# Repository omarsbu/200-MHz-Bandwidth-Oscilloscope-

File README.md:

**This project is intended to be an improvement on a previous version that can be seen here:**
https://github.com/omarsbu/1MHz-Bandwidth-Oscilloscope/tree/main/100kHz%20Oscilloscope

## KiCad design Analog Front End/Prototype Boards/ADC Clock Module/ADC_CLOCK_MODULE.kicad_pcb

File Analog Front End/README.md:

The purpose of an analog front end is to condition the input signal so that it maximizes the ADC’s dynamic range and limits the bandwidth to the ADC’s Nyquist frequency. Attenuators extend the measurable range by scaling down large input signals to within the appropriate voltage range and a programmable gain amplifier boosts small signals so they make full use of the ADC’s resolution. DC offsetting is also applied to bias the signal so that it fits well within the ADC’s input range. A high impedance JFET LNA buffer allows the oscilloscope input to be terminated with 1 MΩ or 50 Ω impedance.

The input stage of each channel consists of a set of relay switches to select between AC and DC coupling, as well as different attenuation levels. A compensated 1 MΩ L-pad attenuator is used for normal measurements with standard probes, while 50 Ω pi-attenuators are used for high-fidelity measurements from a 50 Ω source. Protection diodes clamp the input voltage if it exceeds the positive or negative supply rails.

The BUF802 is used in conjunction with the OPA140 to form a composite amplifier that delivers strong performance at both high and low frequencies. The BUF802, with its JFET input, provides exceptional AC performance but poor DC precision, while the OPA140 offers excellent DC precision but lacks sufficient bandwidth and slew rate for high-frequency signals. To leverage the strengths of both, the main input is AC-coupled to the BUF802, while the auxiliary input is driven by the OPA140’s DC offset circuitry. This circuitry uses a differential amplifier along with a DAC (0–5 V) and a 2.5 V reference to shift the output within a programmable range of ±2.5 V. A resistor in series with the differential amplifier output allows the DAC to modify the DC feedback network to the OPA140, which drives the BUF802 auxiliary input, thereby enabling a programmable DC offset of the input signal. To prevent the BUF802 output from exceeding the ±1 V differential input range of the LMH6518, Zener diodes are used to clamp the output to ±1 V. Additionally, a 50 Ω series resistor allows the BUF802 to drive the subsequent stages of the analog front-end signal chain as a 50 Ω source.

The ideal input condition of the LMH6518 are shown below:

The LMH6552 functions as a level shifter and single-ended to differential converter with 0 dB gain, providing a balanced differential input with a 2.5 V common-mode voltage to the LMH6518. The single-ended input to the LMH6552 is clamped to ±1 V by the BUF802, ensuring that the LMH6552’s differential output is also limited to ±1 V. The LMH6518 includes programmable bandwidth-limiting filters for anti-aliasing, and its output common-mode voltage is set to match the ADC’s common-mode voltage.

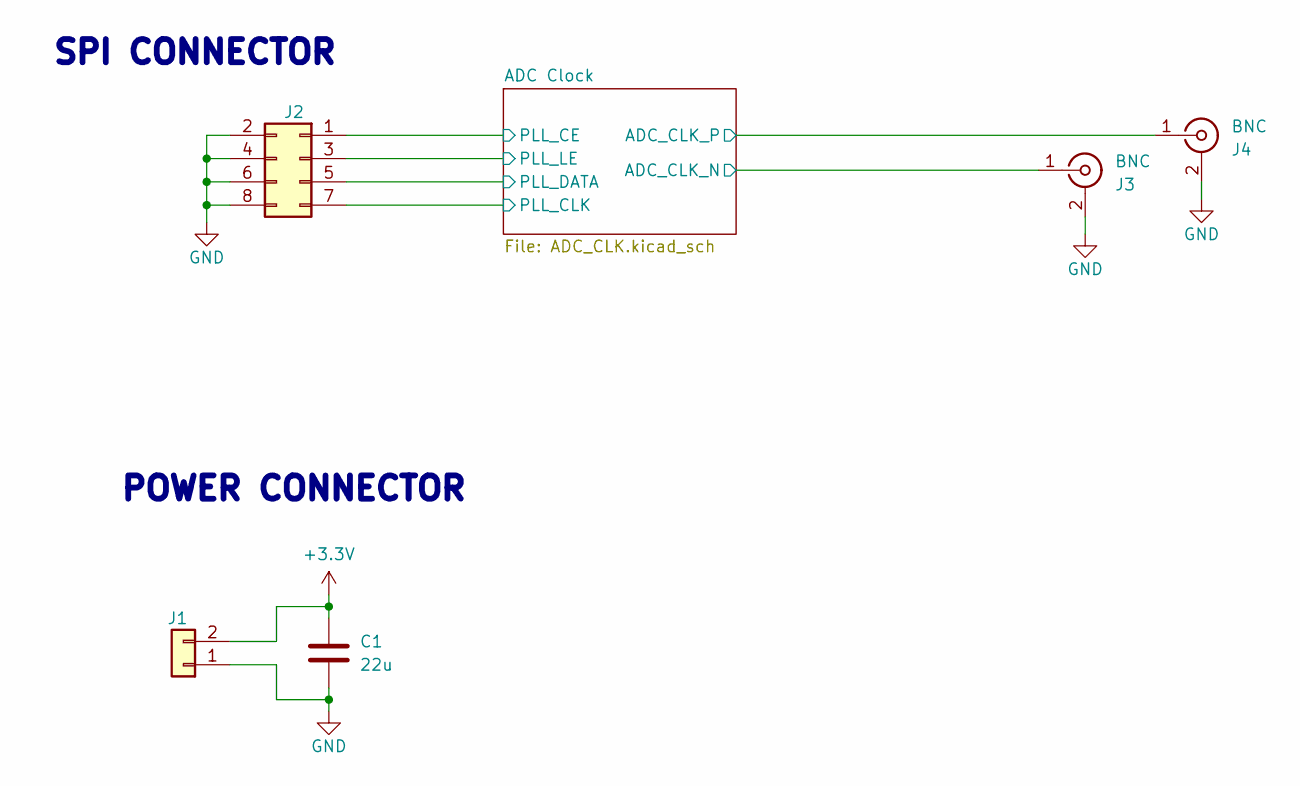
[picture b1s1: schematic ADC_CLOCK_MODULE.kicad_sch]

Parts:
C1: 22u; C_1210_3225Metric_Pad1.33x2.70mm_HandSolder
J1: Conn_01x02; PinHeader_1x02_P2.54mm_Vertical
J2: Conn_02x04_Odd_Even; PinHeader_2x04_P2.54mm_Vertical
J3, J4: BNC; SMA_Amphenol_132289_EdgeMount

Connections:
+3.3V: C1.1, J1.2; also elsewhere on the board
/ADC Clock/ADC_CLK_N: J3.1 (In); also elsewhere on the board
/ADC Clock/ADC_CLK_P: J4.1 (In); also elsewhere on the board
/ADC Clock/PLL_CE: J2.1; also elsewhere on the board
/ADC Clock/PLL_CLK: J2.7; also elsewhere on the board
/ADC Clock/PLL_DATA: J2.5; also elsewhere on the board
/ADC Clock/PLL_LE: J2.3; also elsewhere on the board
GND: C1.2, J1.1, J2.2, J2.4, J2.6, J2.8, J3.2 (Ext), J4.2 (Ext); also elsewhere on the board

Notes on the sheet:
SPI CONNECTOR
POWER CONNECTOR

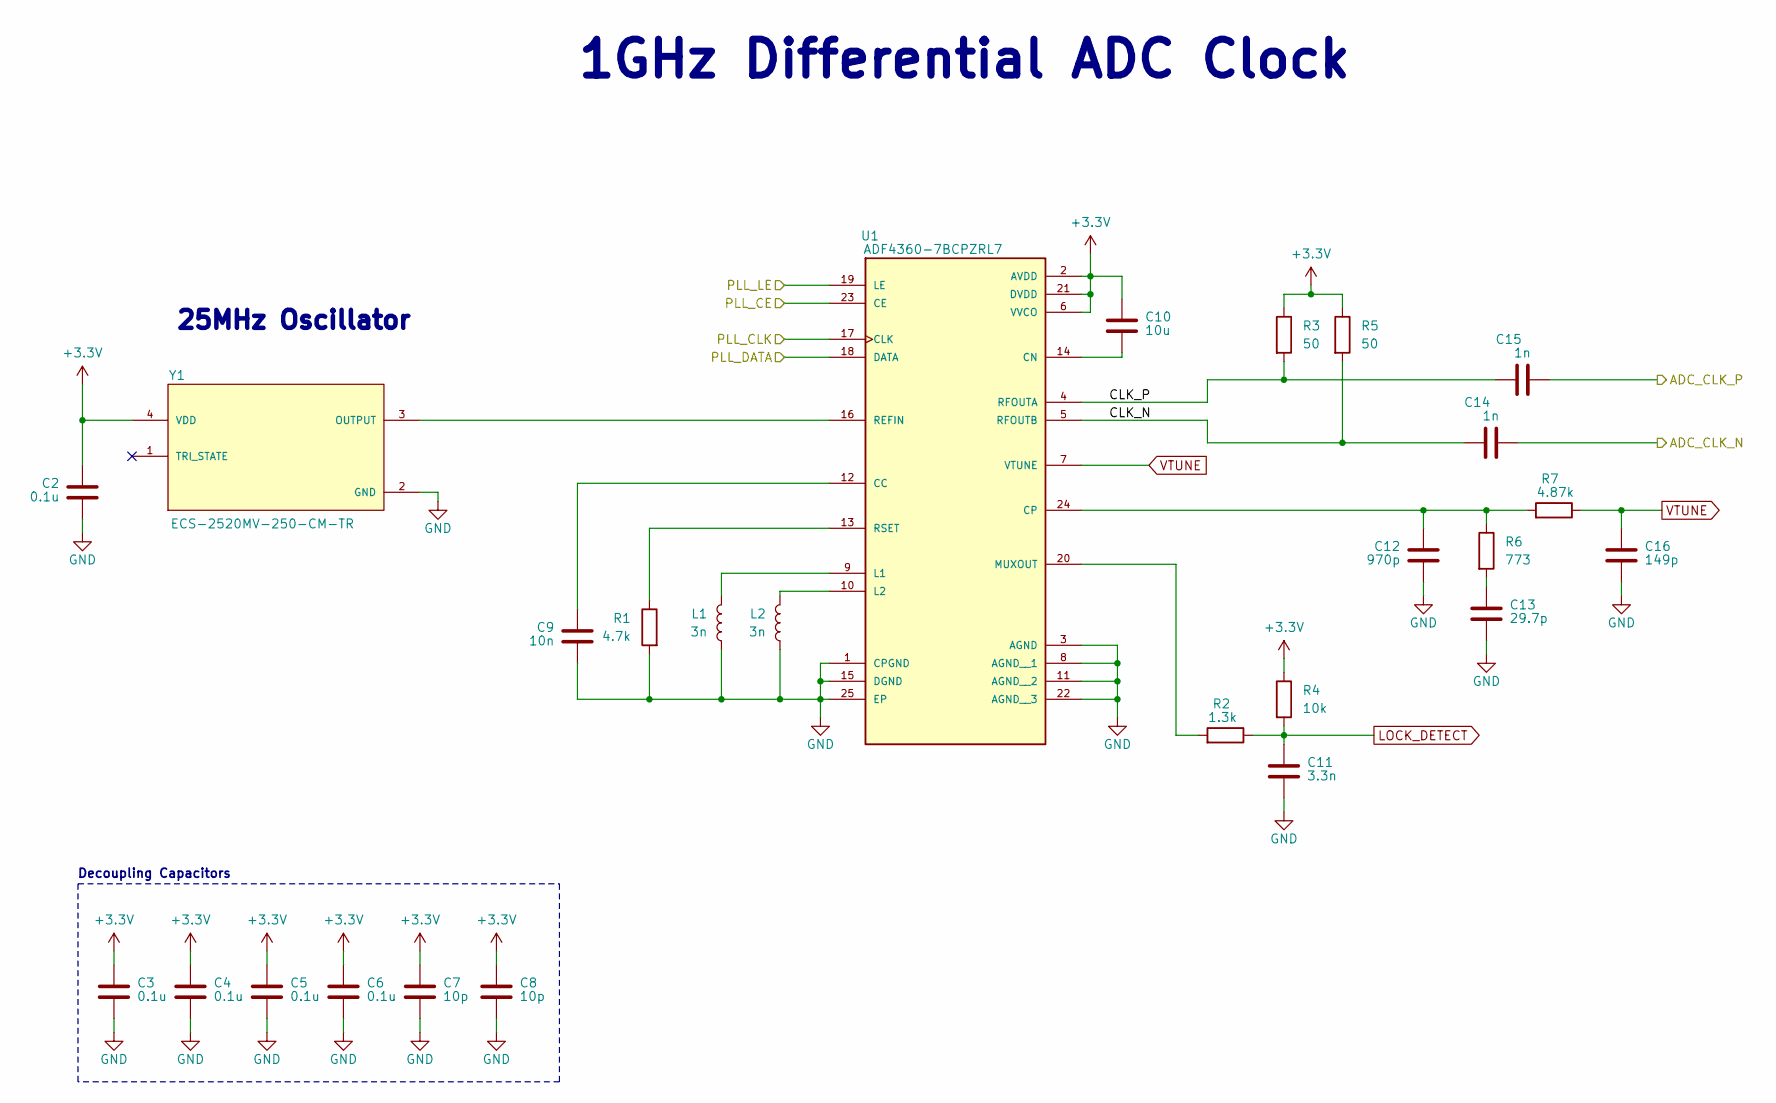
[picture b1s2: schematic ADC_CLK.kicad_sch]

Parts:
C2, C3, C4, C5, C6: 0.1u; C_0603_1608Metric_Pad1.08x0.95mm_HandSolder
C7, C8: 10p; C_0603_1608Metric_Pad1.08x0.95mm_HandSolder
C9: 10n; C_0603_1608Metric_Pad1.08x0.95mm_HandSolder
C10: 10u; C_0603_1608Metric_Pad1.08x0.95mm_HandSolder
C11: 3.3n; C_0603_1608Metric_Pad1.08x0.95mm_HandSolder
C12: 970p; C_0603_1608Metric_Pad1.08x0.95mm_HandSolder
C13: 29.7p; C_0603_1608Metric_Pad1.08x0.95mm_HandSolder
C14, C15: 1n; C_0603_1608Metric_Pad1.08x0.95mm_HandSolder
C16: 149p; C_0603_1608Metric_Pad1.08x0.95mm_HandSolder
L1, L2: 3n; INDC1006X60N
R1: 4.7k; R_0603_1608Metric_Pad0.98x0.95mm_HandSolder
R2: 1.3k; R_0603_1608Metric_Pad0.98x0.95mm_HandSolder
R3, R5: 50; R_0603_1608Metric_Pad0.98x0.95mm_HandSolder
R4: 10k; R_0603_1608Metric_Pad0.98x0.95mm_HandSolder
R6: 773; R_0603_1608Metric_Pad0.98x0.95mm_HandSolder
R7: 4.87k; R_0603_1608Metric_Pad0.98x0.95mm_HandSolder
U1: ADF4360-7BCPZRL7; QFN50P400X400X80-25N; PARTREV F
Y1: ECS-2520MV-250-CM-TR; Oscillator_SMD_ECS_2520MV-xxx-xx-4Pin_2.5x2.0mm

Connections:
+3.3V: C2.1, C3.1, C4.1, C5.1, C6.1, C7.1, C8.1, C10.1, R3.1, R4.1, R5.1, U1.2 (AVDD), U1.6 (VVCO), U1.21 (DVDD), Y1.4 (VDD); also elsewhere on the board
/ADC Clock/ADC_CLK_N: C14.1; also elsewhere on the board
/ADC Clock/ADC_CLK_P: C15.1; also elsewhere on the board
/ADC Clock/CLK_N: C14.2, R5.2, U1.5 (RFOUTB)
/ADC Clock/CLK_P: C15.2, R3.2, U1.4 (RFOUTA)
/ADC Clock/PLL_CE: U1.23 (CE); also elsewhere on the board
/ADC Clock/PLL_CLK: U1.17 (CLK); also elsewhere on the board
/ADC Clock/PLL_DATA: U1.18 (DATA); also elsewhere on the board
/ADC Clock/PLL_LE: U1.19 (LE); also elsewhere on the board
GND: C2.2, C3.2, C4.2, C5.2, C6.2, C7.2, C8.2, C9.2, C11.2, C12.2, C13.2, C16.2, L1.2, L2.2, R1.2, U1.1 (CPGND), U1.3 (AGND), U1.8 (AGND__1), U1.11 (AGND__2), U1.15 (DGND), U1.22 (AGND__3), U1.25 (EP), Y1.2 (GND); also elsewhere on the board
LOCK_DETECT: C11.1, R2.1, R4.2
unnamed: C13.1, R6.2
unnamed: C9.1, U1.12 (CC)
unnamed: C10.2, U1.14 (CN)
unnamed: C12.1, R6.1, R7.2, U1.24 (CP)
unnamed: L1.1, U1.9 (L1)
unnamed: L2.1, U1.10 (L2)
unnamed: R2.2, U1.20 (MUXOUT)
unnamed: U1.16 (REFIN), Y1.3 (OUTPUT)
unnamed: R1.1, U1.13 (RSET)
VTUNE: C16.1, R7.1, U1.7 (VTUNE)

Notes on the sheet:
Decoupling Capacitors
1GHz Differential ADC Clock
25MHz Oscillator

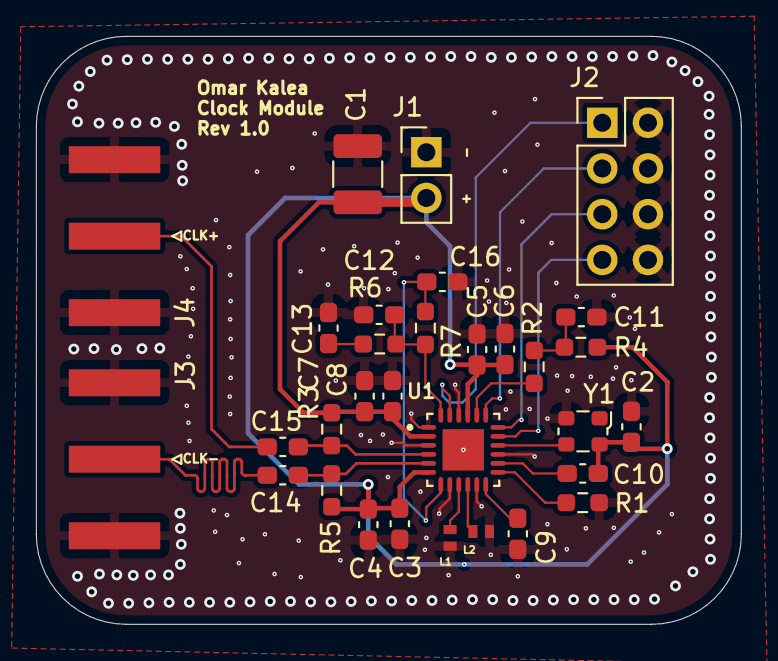
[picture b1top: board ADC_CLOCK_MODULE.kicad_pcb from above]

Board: 4 copper layers, 39.2 x 32.7 mm, 31 parts (0 on the bottom side), 21 nets.

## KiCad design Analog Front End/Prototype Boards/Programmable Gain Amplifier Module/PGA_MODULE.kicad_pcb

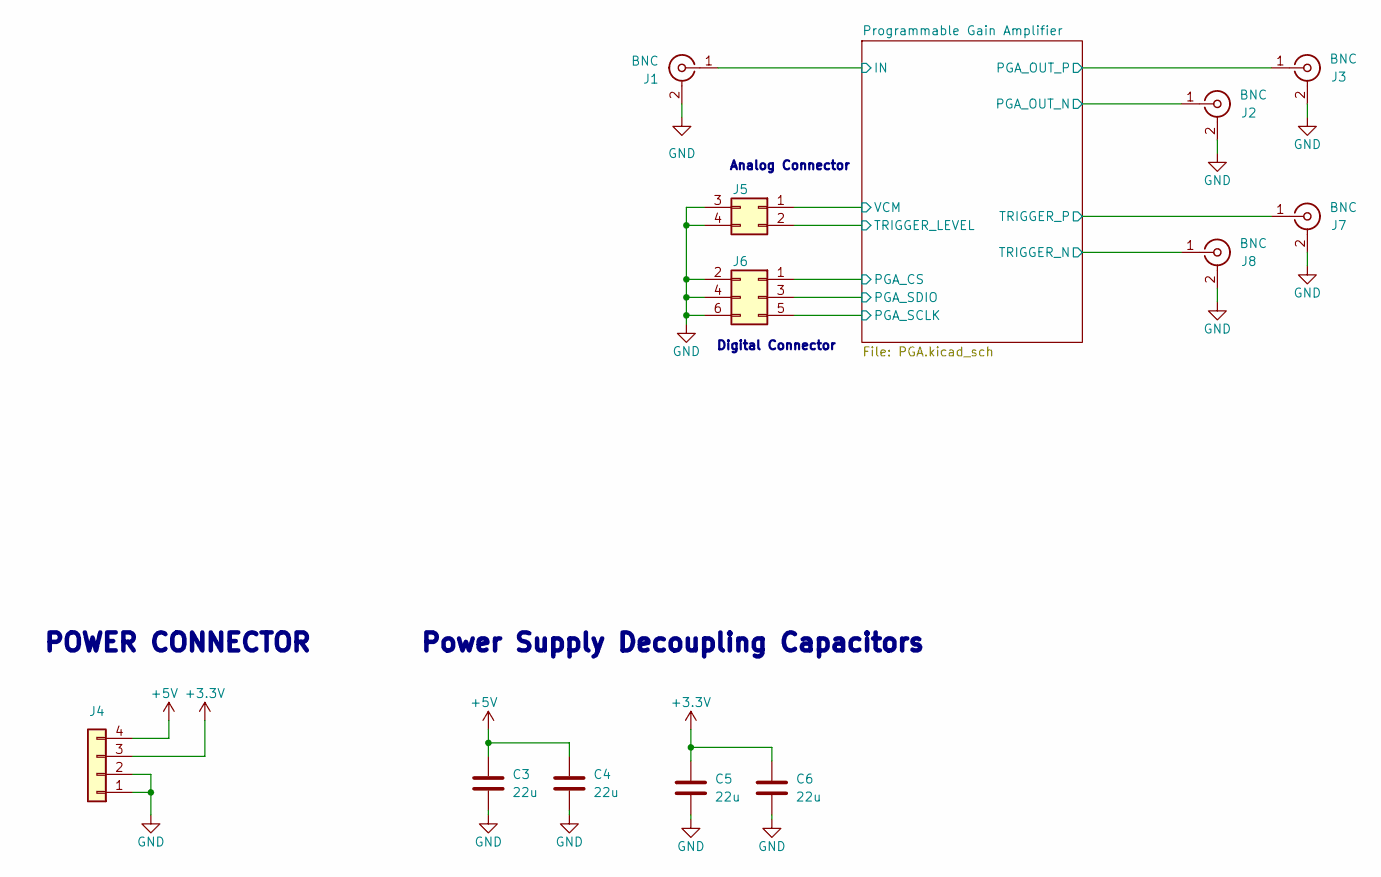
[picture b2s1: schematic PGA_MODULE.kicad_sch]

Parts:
C3, C4, C5, C6: 22u; C_1210_3225Metric_Pad1.33x2.70mm_HandSolder
J1, J2, J3, J7, J8: BNC; CONN_73100-0105_MOL
J4: Conn_01x04; PinHeader_2x02_P2.54mm_Vertical
J5: Conn_02x02_Top_Bottom; PinHeader_2x02_P2.54mm_Vertical
J6: Conn_02x03_Odd_Even; PinSocket_2x03_P2.54mm_Vertical

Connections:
+3.3V: C5.1, C6.1, J4.3; also elsewhere on the board
+5V: C3.1, C4.1, J4.4; also elsewhere on the board
/Programmable Gain Amplifier/IN: J1.1 (In); also elsewhere on the board
/Programmable Gain Amplifier/PGA_CS: J6.1; also elsewhere on the board
/Programmable Gain Amplifier/PGA_OUT_N: J2.1 (In); also elsewhere on the board
/Programmable Gain Amplifier/PGA_OUT_P: J3.1 (In); also elsewhere on the board
/Programmable Gain Amplifier/PGA_SCLK: J6.5; also elsewhere on the board
/Programmable Gain Amplifier/PGA_SDIO: J6.3; also elsewhere on the board
/Programmable Gain Amplifier/TRIGGER_LEVEL: J5.2; also elsewhere on the board
/Programmable Gain Amplifier/TRIGGER_N: J8.1 (In); also elsewhere on the board
/Programmable Gain Amplifier/TRIGGER_P: J7.1 (In); also elsewhere on the board
/Programmable Gain Amplifier/VCM: J5.1; also elsewhere on the board
GND: C3.2, C4.2, C5.2, C6.2, J1.2 (Ext), J1.3, J2.2 (Ext), J2.3, J3.2 (Ext), J3.3, J4.1, J4.2, J5.3, J5.4, J6.2, J6.4, J6.6, J7.2 (Ext), J7.3, J8.2 (Ext), J8.3; also elsewhere on the board

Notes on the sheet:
Analog Connector
Digital Connector
POWER CONNECTOR
Power Supply Decoupling Capacitors

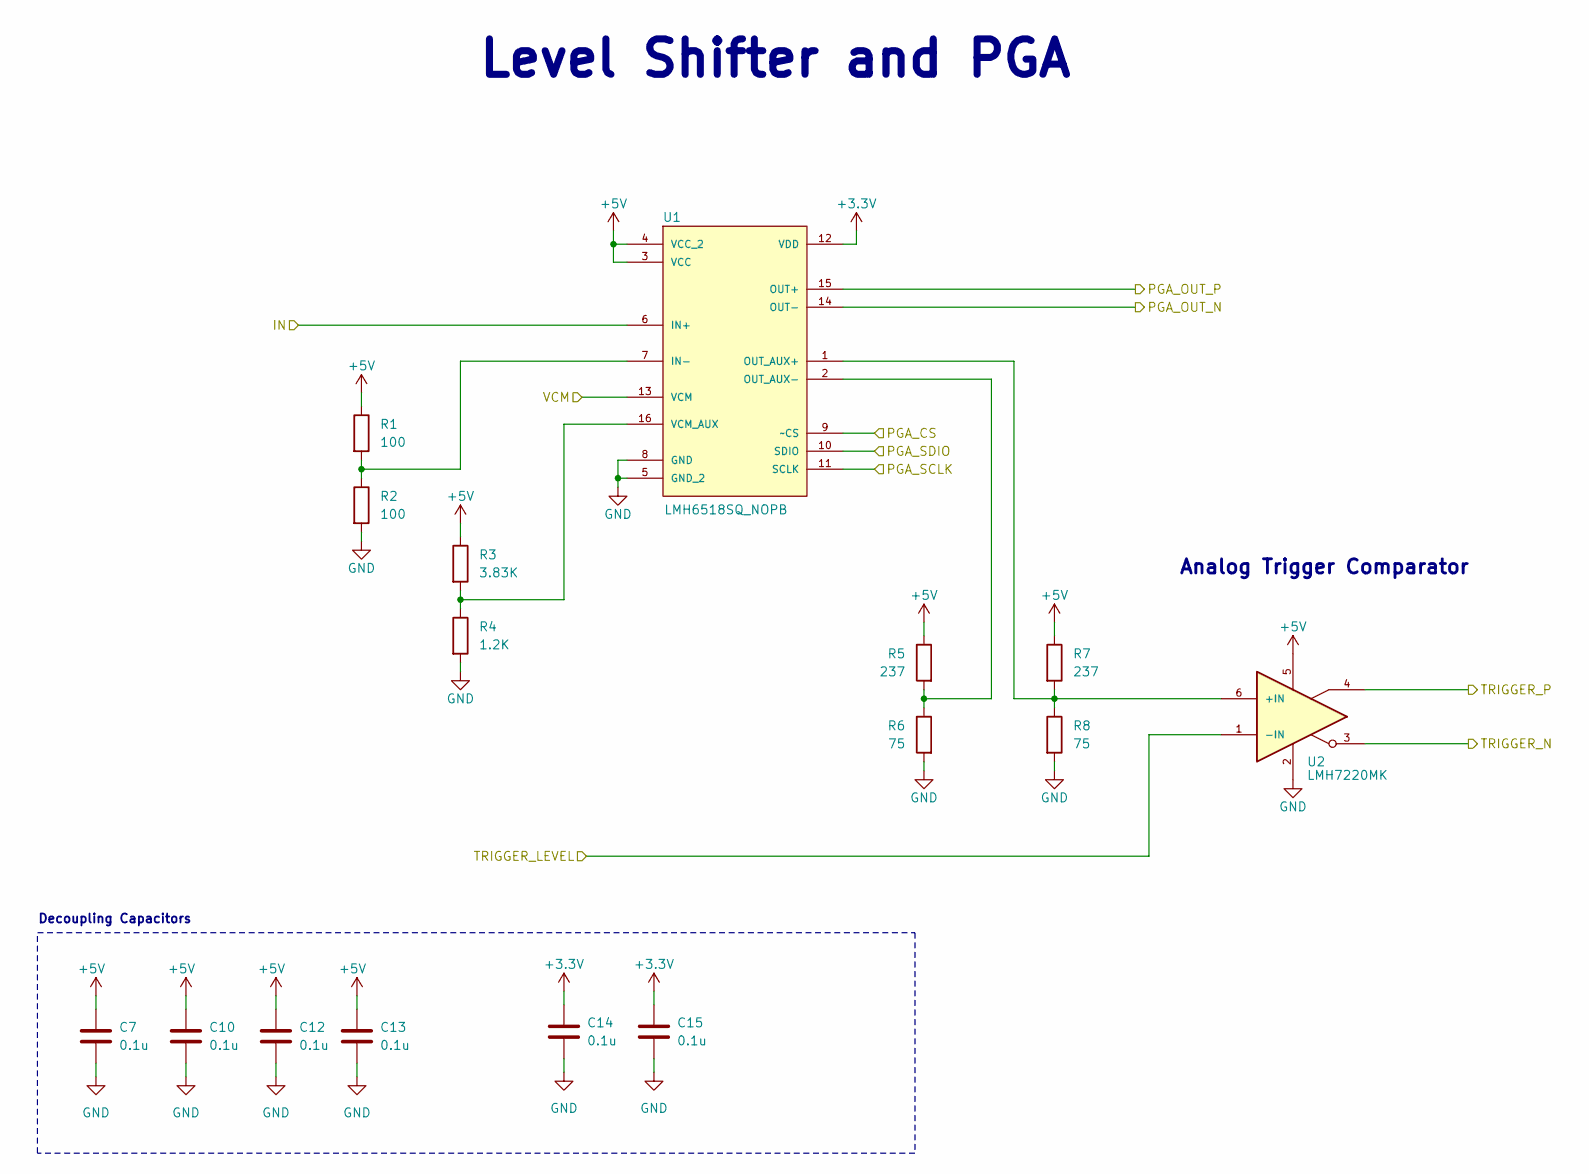
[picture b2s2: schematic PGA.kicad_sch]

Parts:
C7, C10, C12, C13, C14, C15: 0.1u; C_0603_1608Metric
R1, R2: 100; R_0603_1608Metric_Pad0.98x0.95mm_HandSolder
R3: 3.83K; R_0603_1608Metric_Pad0.98x0.95mm_HandSolder
R4: 1.2K; R_0603_1608Metric_Pad0.98x0.95mm_HandSolder
R5, R7: 237; R_0603_1608Metric_Pad0.98x0.95mm_HandSolder
R6, R8: 75; R_0603_1608Metric_Pad0.98x0.95mm_HandSolder
U1: LMH6518SQ_NOPB; QFN50P400X400X80-17N; MPN LMH6518SQ/NOPB
U2: LMH7220MK; SOT95P280X110-6N

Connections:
+3.3V: C14.1, C15.1, U1.12 (VDD); also elsewhere on the board
+5V: C7.1, C10.1, C12.1, C13.1, R1.1, R3.1, R5.1, R7.1, U1.3 (VCC), U1.4 (VCC_2), U2.5; also elsewhere on the board
/Programmable Gain Amplifier/IN: U1.6 (IN+); also elsewhere on the board
/Programmable Gain Amplifier/PGA_CS: U1.9 (~CS); also elsewhere on the board
/Programmable Gain Amplifier/PGA_OUT_N: U1.14 (OUT-); also elsewhere on the board
/Programmable Gain Amplifier/PGA_OUT_P: U1.15 (OUT+); also elsewhere on the board
/Programmable Gain Amplifier/PGA_SCLK: U1.11 (SCLK); also elsewhere on the board
/Programmable Gain Amplifier/PGA_SDIO: U1.10 (SDIO); also elsewhere on the board
/Programmable Gain Amplifier/TRIGGER_LEVEL: U2.1 (-IN); also elsewhere on the board
/Programmable Gain Amplifier/TRIGGER_N: U2.3; also elsewhere on the board
/Programmable Gain Amplifier/TRIGGER_P: U2.4; also elsewhere on the board
/Programmable Gain Amplifier/VCM: U1.13 (VCM); also elsewhere on the board
GND: C7.2, C10.2, C12.2, C13.2, C14.2, C15.2, R2.2, R4.2, R6.2, R8.2, U1.5 (GND_2), U1.8 (GND), U1.17, U2.2; also elsewhere on the board
unnamed: R1.2, R2.1, U1.7 (IN-)
unnamed: R7.2, R8.1, U1.1 (OUT_AUX+), U2.6 (+IN)
unnamed: R5.2, R6.1, U1.2 (OUT_AUX-)
unnamed: R3.2, R4.1, U1.16 (VCM_AUX)

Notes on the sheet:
Decoupling Capacitors
Analog Trigger Comparator
Level Shifter and PGA

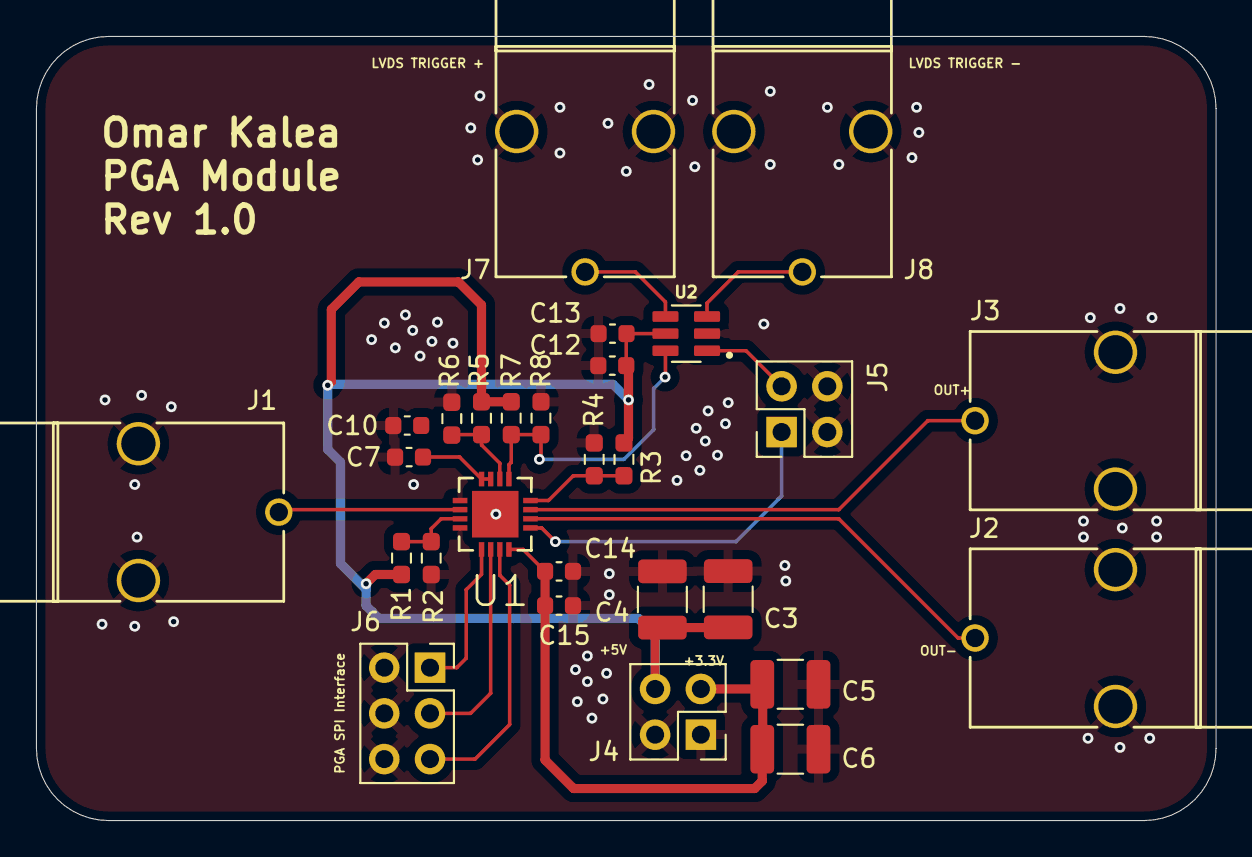
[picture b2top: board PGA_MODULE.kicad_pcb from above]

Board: 4 copper layers, 65.5 x 43.6 mm, 28 parts (0 on the bottom side), 17 nets.

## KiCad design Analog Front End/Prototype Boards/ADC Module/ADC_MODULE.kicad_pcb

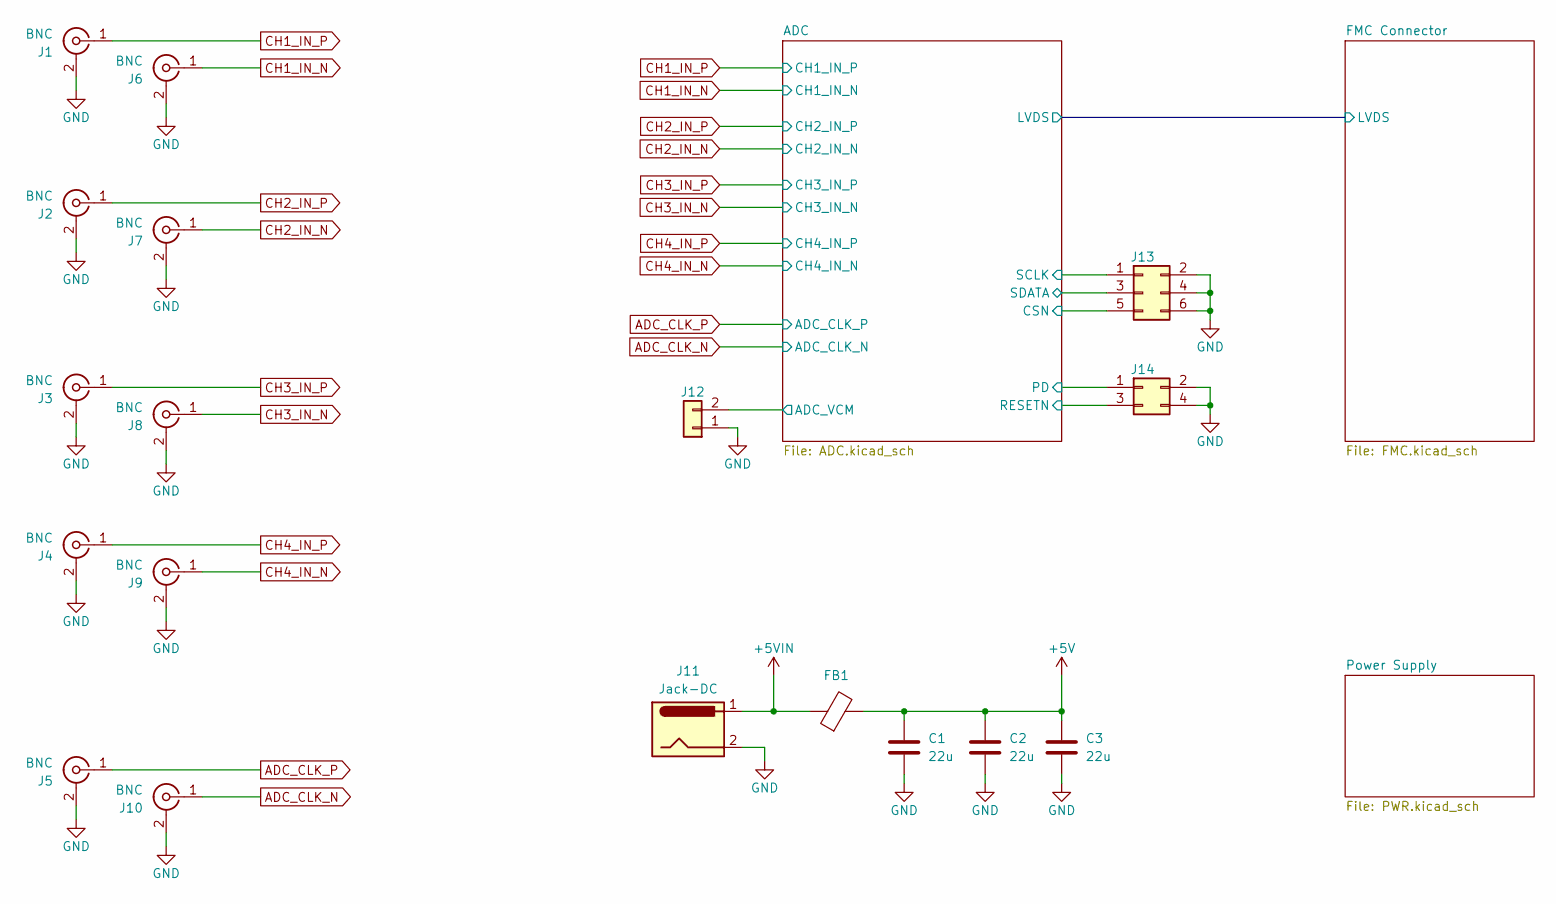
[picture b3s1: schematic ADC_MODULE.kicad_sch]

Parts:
C1, C2, C3: 22u; C_1210_3225Metric_Pad1.33x2.70mm_HandSolder
FB1: FerriteBead; BEADC1005X55N
J1, J2, J3, J4, J6, J7, J8, J9: BNC; SMA_Amphenol_132289_EdgeMount
J5, J10: BNC; SMA_Amphenol_132134_Vertical
J11: Jack-DC; BarrelJack_Kycon_KLDX-0202-xC_Horizontal
J12: Conn_01x02; PinHeader_1x02_P2.54mm_Vertical
J13: Conn_02x03_Odd_Even; PinHeader_2x03_P2.54mm_Vertical
J14: Conn_02x02_Odd_Even; PinHeader_2x02_P2.54mm_Vertical

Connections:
+5V: C1.1, C2.1, C3.1, FB1.2; also elsewhere on the board
+5VIN: FB1.1, J11.1
/ADC/ADC_VCM: J12.2; also elsewhere on the board
/ADC/CSN: J13.5; also elsewhere on the board
/ADC/PD: J14.1; also elsewhere on the board
/ADC/RESETN: J14.3; also elsewhere on the board
/ADC/SCLK: J13.1; also elsewhere on the board
/ADC/SDATA: J13.3; also elsewhere on the board
ADC_CLK_N: J10.1 (In); also elsewhere on the board
ADC_CLK_P: J5.1 (In); also elsewhere on the board
CH1_IN_N: J6.1 (In); also elsewhere on the board
CH1_IN_P: J1.1 (In); also elsewhere on the board
CH2_IN_N: J7.1 (In); also elsewhere on the board
CH2_IN_P: J2.1 (In); also elsewhere on the board
CH3_IN_N: J8.1 (In); also elsewhere on the board
CH3_IN_P: J3.1 (In); also elsewhere on the board
CH4_IN_N: J9.1 (In); also elsewhere on the board
CH4_IN_P: J4.1 (In); also elsewhere on the board
GND: C1.2, C2.2, C3.2, J1.2 (Ext), J2.2 (Ext), J3.2 (Ext), J4.2 (Ext), J5.2 (Ext), J6.2 (Ext), J7.2 (Ext), J8.2 (Ext), J9.2 (Ext), J10.2 (Ext), J11.2, J11.3, J12.1, J13.2, J13.4, J13.6, J14.2, J14.4; also elsewhere on the board

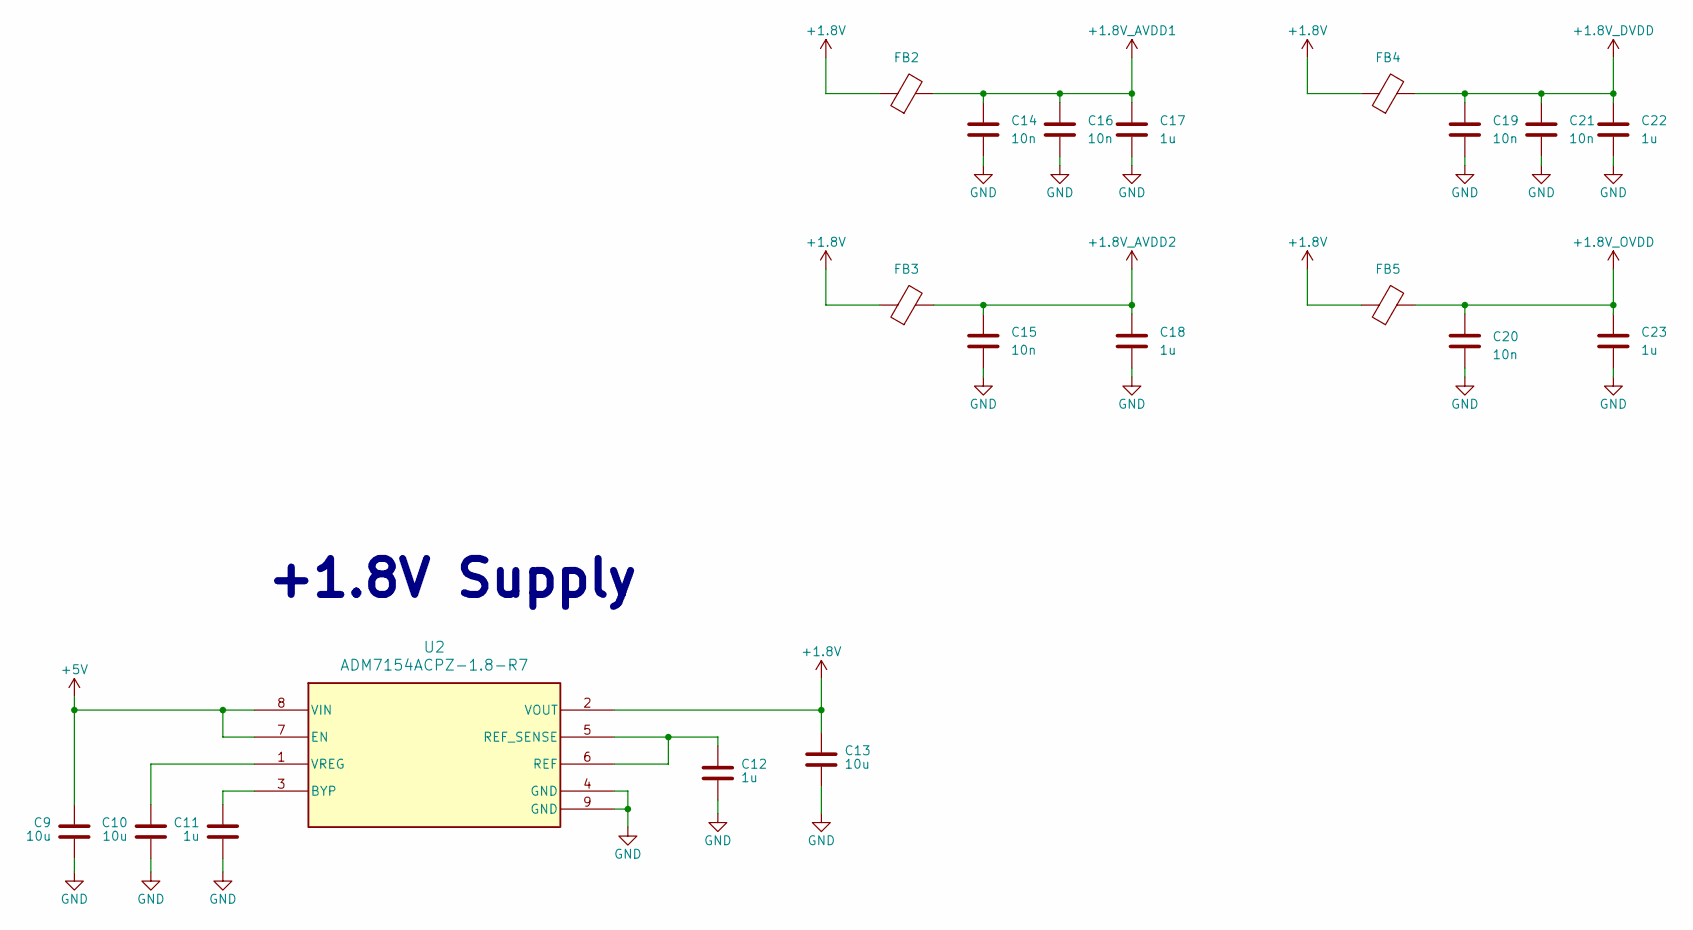
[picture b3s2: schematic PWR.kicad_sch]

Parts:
C9, C10, C13: 10u; C_0603_1608Metric_Pad1.08x0.95mm_HandSolder
C11, C12, C17, C18, C22, C23: 1u; C_0603_1608Metric_Pad1.08x0.95mm_HandSolder
C14, C15, C16, C19, C20, C21: 10n; C_0603_1608Metric_Pad1.08x0.95mm_HandSolder
FB2, FB3, FB4, FB5: FerriteBead; BEADC1005X55N
U2: ADM7154ACPZ-1.8-R7; ADM7154ARDZ_1_8_R7

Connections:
+1.8V: C13.1, FB2.1, FB3.1, FB4.1, FB5.1, U2.2 (VOUT)
+1.8V_AVDD1: C14.2, C16.2, C17.2, FB2.2; also elsewhere on the board
+1.8V_AVDD2: C15.2, C18.2, FB3.2; also elsewhere on the board
+1.8V_DVDD: C19.2, C21.2, C22.2, FB4.2; also elsewhere on the board
+1.8V_OVDD: C20.2, C23.2, FB5.2; also elsewhere on the board
+5V: C9.1, U2.7 (EN), U2.8 (VIN); also elsewhere on the board
GND: C9.2, C10.2, C11.2, C12.2, C13.2, C14.1, C15.1, C16.1, C17.1, C18.1, C19.1, C20.1, C21.1, C22.1, C23.1, U2.4 (GND), U2.9 (GND); also elsewhere on the board
unnamed: C11.1, U2.3 (BYP)
unnamed: C12.1, U2.5 (REF_SENSE), U2.6 (REF)
unnamed: C10.1, U2.1 (VREG)

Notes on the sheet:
+1.8V Supply

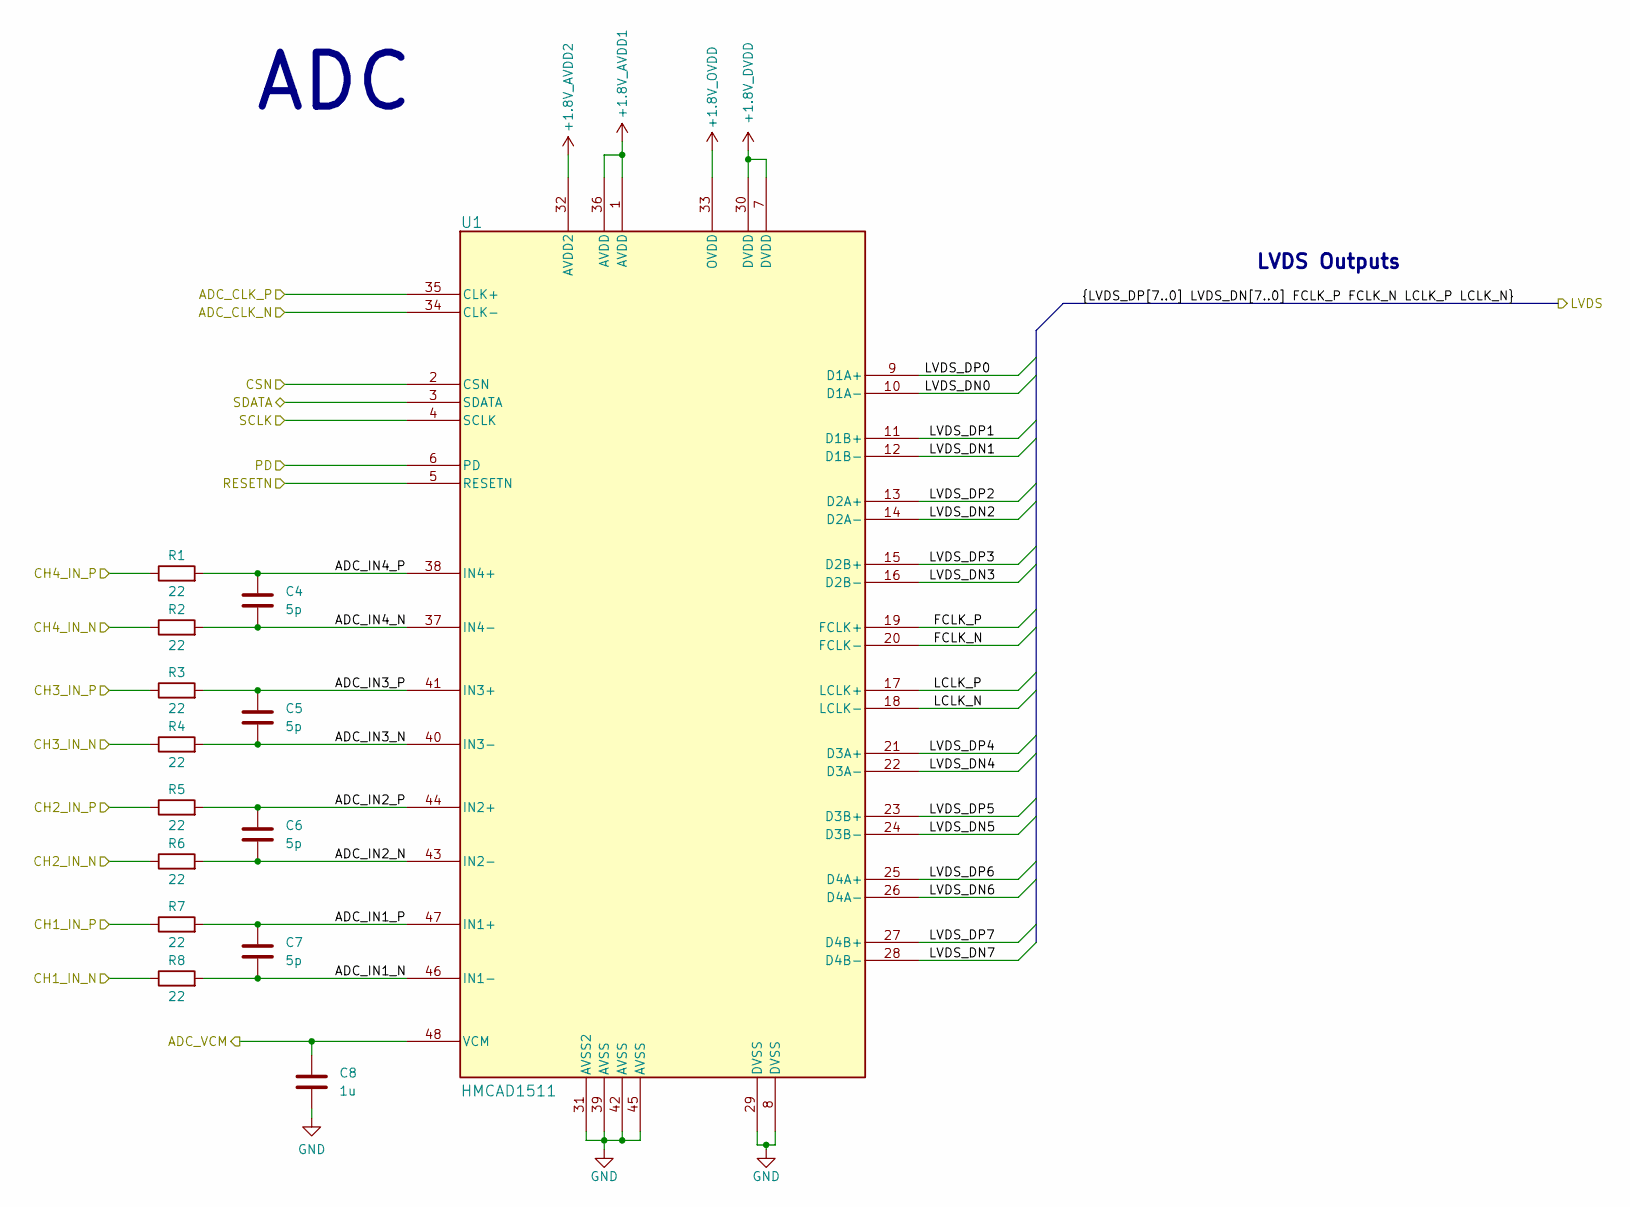
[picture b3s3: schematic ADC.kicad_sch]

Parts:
C4, C5, C6, C7: 5p; C_0603_1608Metric_Pad1.08x0.95mm_HandSolder
C8: 1u; C_0603_1608Metric_Pad1.08x0.95mm_HandSolder
R1, R2, R3, R4, R5, R6, R7, R8: 22; R_0603_1608Metric_Pad0.98x0.95mm_HandSolder
U1: HMCAD1511; CP-48-22_ADI-L

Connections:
+1.8V_AVDD1: U1.1 (AVDD), U1.36 (AVDD); also elsewhere on the board
+1.8V_AVDD2: U1.32 (AVDD2); also elsewhere on the board
+1.8V_DVDD: U1.7 (DVDD), U1.30 (DVDD); also elsewhere on the board
+1.8V_OVDD: U1.33 (OVDD); also elsewhere on the board
/ADC/ADC_IN1_N: C7.1, R8.2, U1.46 (IN1-)
/ADC/ADC_IN1_P: C7.2, R7.2, U1.47 (IN1+)
/ADC/ADC_IN2_N: C6.1, R6.2, U1.43 (IN2-)
/ADC/ADC_IN2_P: C6.2, R5.2, U1.44 (IN2+)
/ADC/ADC_IN3_N: C5.1, R4.2, U1.40 (IN3-)
/ADC/ADC_IN3_P: C5.2, R3.2, U1.41 (IN3+)
/ADC/ADC_IN4_N: C4.1, R2.2, U1.37 (IN4-)
/ADC/ADC_IN4_P: C4.2, R1.2, U1.38 (IN4+)
/ADC/ADC_VCM: C8.2, U1.48 (VCM); also elsewhere on the board
/ADC/CSN: U1.2 (CSN); also elsewhere on the board
/ADC/FCLK_N: U1.20 (FCLK-); also elsewhere on the board
/ADC/FCLK_P: U1.19 (FCLK+); also elsewhere on the board
/ADC/LCLK_N: U1.18 (LCLK-); also elsewhere on the board
/ADC/LCLK_P: U1.17 (LCLK+); also elsewhere on the board
/ADC/LVDS_DN0: U1.10 (D1A-); also elsewhere on the board
/ADC/LVDS_DN1: U1.12 (D1B-); also elsewhere on the board
/ADC/LVDS_DN2: U1.14 (D2A-); also elsewhere on the board
/ADC/LVDS_DN3: U1.16 (D2B-); also elsewhere on the board
/ADC/LVDS_DN4: U1.22 (D3A-); also elsewhere on the board
/ADC/LVDS_DN5: U1.24 (D3B-); also elsewhere on the board
/ADC/LVDS_DN6: U1.26 (D4A-); also elsewhere on the board
/ADC/LVDS_DN7: U1.28 (D4B-); also elsewhere on the board
/ADC/LVDS_DP0: U1.9 (D1A+); also elsewhere on the board
/ADC/LVDS_DP1: U1.11 (D1B+); also elsewhere on the board
/ADC/LVDS_DP2: U1.13 (D2A+); also elsewhere on the board
/ADC/LVDS_DP3: U1.15 (D2B+); also elsewhere on the board
/ADC/LVDS_DP4: U1.21 (D3A+); also elsewhere on the board
/ADC/LVDS_DP5: U1.23 (D3B+); also elsewhere on the board
/ADC/LVDS_DP6: U1.25 (D4A+); also elsewhere on the board
/ADC/LVDS_DP7: U1.27 (D4B+); also elsewhere on the board
/ADC/PD: U1.6 (PD); also elsewhere on the board
/ADC/RESETN: U1.5 (RESETN); also elsewhere on the board
/ADC/SCLK: U1.4 (SCLK); also elsewhere on the board
/ADC/SDATA: U1.3 (SDATA); also elsewhere on the board
ADC_CLK_N: U1.34 (CLK-); also elsewhere on the board
ADC_CLK_P: U1.35 (CLK+); also elsewhere on the board
CH1_IN_N: R8.1; also elsewhere on the board
CH1_IN_P: R7.1; also elsewhere on the board
CH2_IN_N: R6.1; also elsewhere on the board
CH2_IN_P: R5.1; also elsewhere on the board
CH3_IN_N: R4.1; also elsewhere on the board
CH3_IN_P: R3.1; also elsewhere on the board
CH4_IN_N: R2.1; also elsewhere on the board
CH4_IN_P: R1.1; also elsewhere on the board
GND: C8.1, U1.8 (DVSS), U1.29 (DVSS), U1.31 (AVSS2), U1.39 (AVSS), U1.42 (AVSS), U1.45 (AVSS), U1.49; also elsewhere on the board

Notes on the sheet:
ADC
LVDS Outputs
